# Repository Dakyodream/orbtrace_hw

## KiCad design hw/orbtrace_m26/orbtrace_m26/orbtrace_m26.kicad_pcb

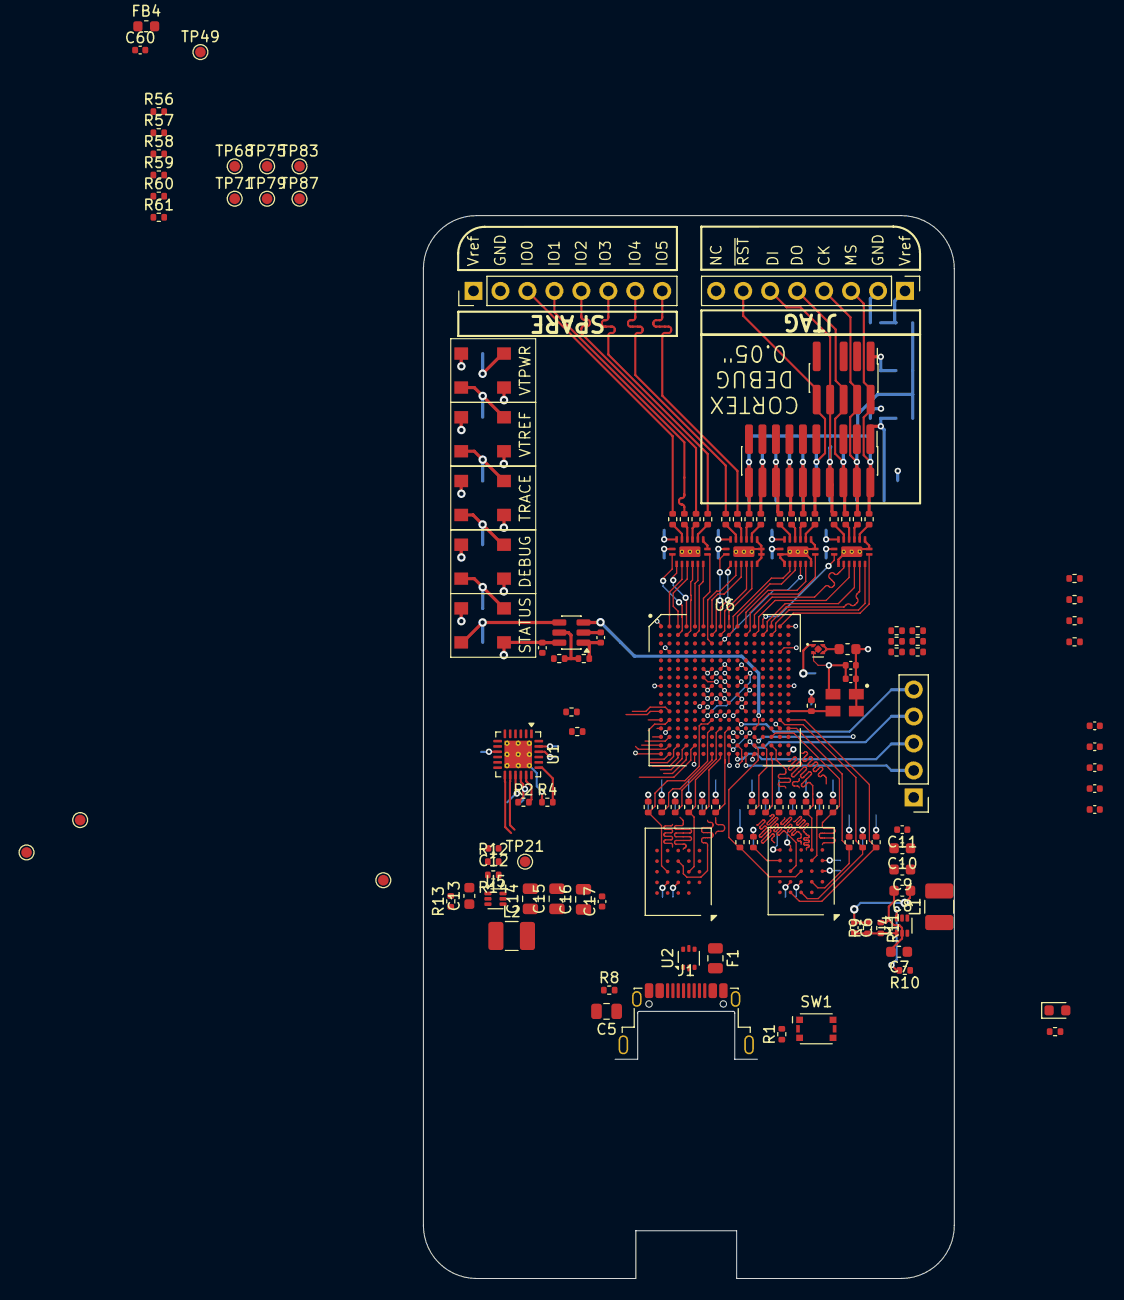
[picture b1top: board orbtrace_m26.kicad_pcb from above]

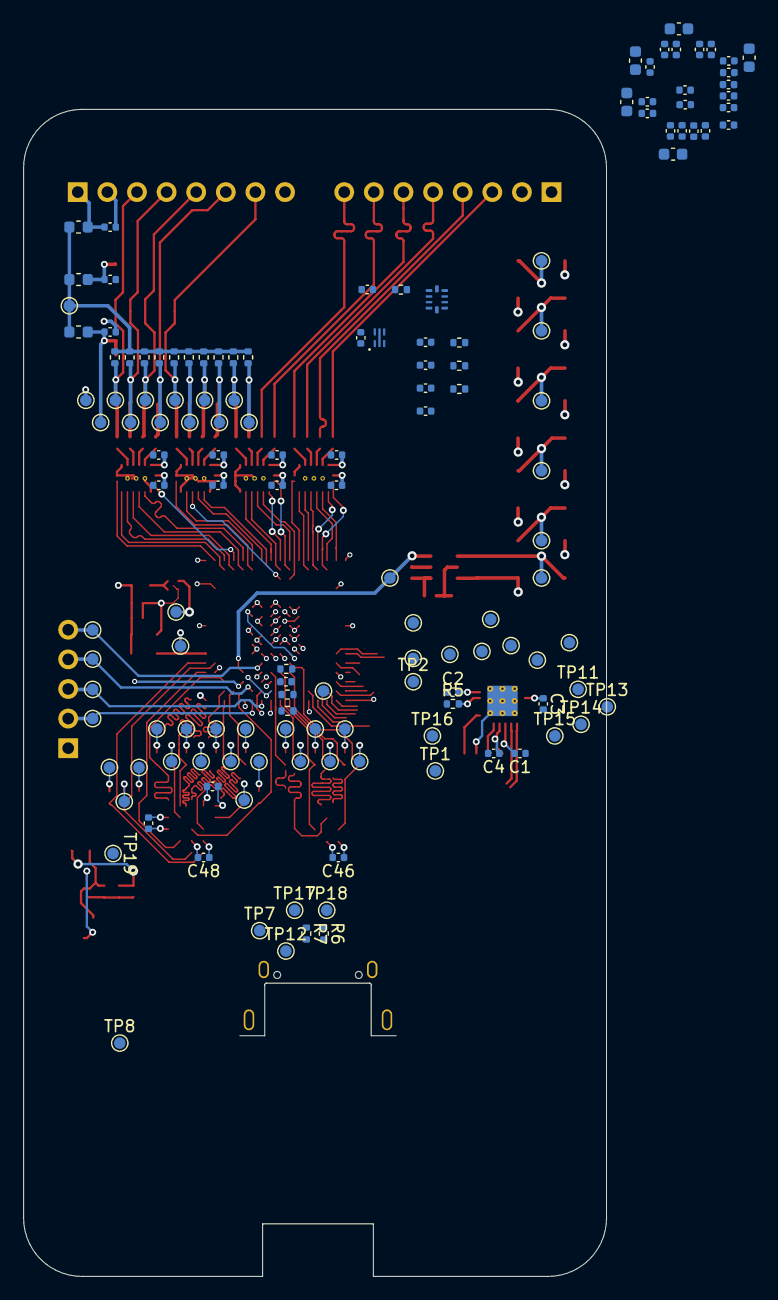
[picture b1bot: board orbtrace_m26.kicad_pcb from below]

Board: 4 copper layers, 50.0 x 100.1 mm, 273 parts (141 on the bottom side), 161 nets.

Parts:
C1, C2, C11, C17, C44: 1µF; C_0402_1005Metric
C3, C4, C18, C22, C23, C24, C25, C26, C27, C29, C30, C32, C33, C34, C35, C36, C37, C38, C39, C40, C41, C42, C43, C45, C46, C47, C48, C49, C50, C51, C52, C53, C54, C55, C56, C57, C58, C59, C60, C61, C62, C71, C72, C73, C74, C75, C76, C77: 100nF; C_0402_1005Metric
C5: 4.7nF; C_0805_2012Metric
C6, C12: 6.8pF; C_0402_1005Metric
C7, C13: 4.7µF; C_0603_1608Metric
C8, C9, C10, C19, C20, C21, C28, C31: 10µF; C_0603_1608Metric
C14, C15, C16: 22µF; C_0805_2012Metric
C63, C64, C65, C66: 470nF; C_0402_1005Metric
D1: GREEN; LED_0603_1608Metric
F1: 500mA; Fuse_0805_2012Metric
FB1, FB2, FB3, FB4, FB5: MMZ1005Y121CT000; L_0603_1608Metric
J1: USB_C_Receptacle_USB2.0_16P; USB_C_Receptacle_Amphenol_12401948E412A
J2: Conn_01x05; PinHeader_1x05_P2.54mm_Vertical
J3, J4: Conn_01x08; PinHeader_1x08_P2.54mm_Vertical
L1, L2: 2.2µH; L_1210_3225Metric_Pad1.42x2.65mm_HandSolder
R1, R5: 10k; R_0402_1005Metric
R2: 20k; R_0402_1005Metric
R3: 180Ω; R_0402_1005Metric
R4: 8.06k; R_0402_1005Metric
R6, R7: 5.1k; R_0402_1005Metric
R8: 1M; R_0402_1005Metric
R9: 453k; R_0402_1005Metric
R10, R13: 475k; R_0402_1005Metric
R11, R14, R38, R39, R40, R41, R44, R49, R52, R53, R54, R55, R56, R57, R58, R59, R60, R61: 100k; R_0402_1005Metric
R12: 82.5k; R_0402_1005Metric
R15, R16, R17, R18, R19, R20, R21, R22, R23, R24, R25, R26: 4.7k; R_0402_1005Metric
R27, R28, R29, R68, R69, R70, R71, R72, R73, R74, R75, R76, R77, R78, R79, R80, R81, R82, R83, R84, R85, R86: 0Ω; R_0402_1005Metric
R30, R31, R32, R33, R34, R35, R36, R37, R42, R43, R45, R46, R47, R48, R50, R51: 100Ω; R_0402_1005Metric
R62, R63, R64, R65, R66, R67: 1K; R_0402_1005Metric
SW1: SW_Push_Shielded; SW_Wurth_WS-TASV_435151014824
TP1, TP2, TP3, TP4, TP5, TP6, TP7, TP8, TP9, TP10, TP11, TP12, TP13, TP14, TP15, TP16, TP17, TP18, TP19, TP20, TP21, TP22, TP23, TP24, TP25, TP26, TP27, TP28, TP29, TP30, TP31, TP32, TP33, TP34, TP35, TP36, TP37, TP38, TP39, TP40, TP41, TP42, TP43, TP44, TP45, TP46, TP47, TP48, TP49, TP52, TP53, TP56, TP59, TP62, TP65, TP68, TP69, TP71, TP72, TP75, TP76, TP79, TP80, TP83, TP84, TP87, TP93, TP94, TP95, TP96, TP97, TP98, TP99, TP100, TP101, TP102, TP103: TestPoint_Pad_D1.0mm
U1: USB3343; QFN-24-1EP_4x4mm_P0.5mm_EP2.6x2.6mm_ThermalVias
U2: USBLC6-2P6; SOT-666
U3: TLV71325PDQN; Texas_X2SON-4_1x1mm_P0.65mm
U4, U5: TLV62568PDRL; SOT-563
U6: LFE5U-25F-6BG256C; lattice_caBGA-256_ECP5
U7: M24128-BFMH; UFDFPN5
U8: W956A8MBYA5I; BGA-24_6x8mm_Layout5x5_P1.0mm
U9: S25FL064LABBHV020; BGA-24_6x8mm_Layout5x5_P1.0mm
U10: SWD-TRACE-FTSH110; PinSocket_2x10_P1.27mm_JTAG
U11, U12, U14, U15: SN74AVC4T774-Q1; TI-WQFN-BQB0016B
U13: SWD-FTSH105; PinSocket_2x05_P1.27mm_JTAG
U16: TLA2024; RUG0010A
U17: SN74LVC1T45DBV; SOT-23-6
U18, U19, U20, U21, U22: WL-ICLED; LED_RGB_Wuerth-PLCC4_5x5mm_WL-ICLED
Y1: 831025497; CFPS-39

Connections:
+1V1: C12.1, C14.1, C15.1, C16.1, C17.1, C19.1, C20.1, C21.1, C22.1, C23.1, C24.1, C25.1, C26.1, C27.1, L2.2, R12.2, R62.2, TP21.1 (1_1), U6.G6 (VCC), U6.G7 (VCC), U6.G9 (VCC), U6.L8 (VCC), U6.L9 (VCC), U6.L10 (VCC)
+2V5: C28.1, C29.1, C30.1, R63.2, TP20.1 (1_1), U3.1 (OUT), U6.G11 (VCCAUX), U6.L7 (VCCAUX)
+3.3V: C3.1, C6.1, C8.1, C9.1, C10.1, C11.1, C31.1, C32.1, C33.1, C34.1, C35.1, C36.1, C37.1, C38.1, C39.1, C40.1, C41.1, C42.1, C43.1, C46.1, C47.1, C48.1, C49.1, C50.1, C52.1, C55.1, C57.1, C71.1, FB1.1, L1.2, R1.2, R9.2, R15.2, R16.2, R17.2, R18.2, R19.2, R21.2, R22.2, R23.2, R24.2, R25.2, R26.2, R64.2, R66.2, TP19.1 (1_1), U1.2 (CLKOUT), U1.9 (VDDIO), U3.3 (EN), U3.4 (IN), U6.F6 (VCCIO0), U6.F7 (VCCIO0), U6.F10 (VCCIO1), U6.F11 (VCCIO1), U6.H6 (VCCIO7), U6.H7 (VCCIO7), U6.J6 (VCCIO6), U6.J7 (VCCIO6), U6.K11 (VCCIO3), U6.L6 (VCCIO8), U6.L11 (VCCIO3), U7.1 (VCC), U8.B4 (VCC), U8.D1 (VCCQ), U8.E4 (VCCQ), U9.B4 (VCC), U11.16 (VCCA), U12.16 (VCCA), U14.16 (VCCA), U15.16 (VCCA), U17.1 (VCCA)
+5V: C4.1, C7.1, C13.1, C61.1, C72.1, C73.1, C74.1, C75.1, C76.1, C77.1, F1.1, R2.1, R3.2, R10.1, R13.1, TP7.1 (1_1), U1.16 (VBAT), U2.5 (VBUS), U4.3 (VIN), U4.5 (EN), U5.3 (VIN), U5.5 (EN), U16.8 (VDD), U17.6 (VCCB), U18.3 (VDD), U19.3 (VDD), U20.3 (VDD), U21.3 (VDD), U22.3 (VDD)
/FPGA/DONE: R22.1, TP22.1 (1_1), U6.P9 (DONE)
/USB/VBUS: F1.2, J1.A4 (VBUS), J1.A9 (VBUS), J1.B4 (VBUS), J1.B9 (VBUS), TP12.1 (1_1)
BTN: R1.1, SW1.2, TP8.1 (1_1), U6.P12 (PR47D)
CFG0: R24.1, R26.1, R27.2, R29.2, U6.N10 (CFG_0), U6.R10 (CFG_2)
CFG1: R25.1, R28.2, U6.P10 (CFG_1)
DEBUG_JTCK: U6.B13 (PT60A), U11.5 (A3)
DEBUG_JTDI: U6.A12 (PT53B), U11.3 (A1)
DEBUG_JTDO: U6.B12 (PT56A), U11.4 (A2)
DEBUG_JTMS: U6.A14 (PT65B), U11.6 (A4)
DEBUG_NRST: U6.A11 (PT35A), U14.6 (A4)
DIR_JTCK: U6.B14 (PT67A), U11.7 (DIR3)
DIR_JTDI: U6.A13 (PT65A), U11.1 (DIR1)
DIR_JTMS: U6.A15 (PT67B), U11.8 (DIR4)
DIR_NRST: U6.B11 (PT49A), U14.8 (DIR4)
GND: C1.1, C2.1, C3.2, C4.2, C5.2, C7.2, C8.2, C9.2, C10.2, C11.2, C13.2, C14.2, C15.2, C16.2, C17.2, C18.2, C19.2, C20.2, C21.2, C22.2, C23.2, C24.2, C25.2, C26.2, C27.2, C28.2, C29.2, C30.2, C31.2, C32.2, C33.2, C34.2, C35.2, C36.2, C37.2, C38.2, C39.2, C40.2, C41.2, C42.2, C43.2, C44.2, C45.2, C46.2, C47.2, C48.2, C49.2, C50.2, C51.2, C52.2, C53.2, C54.2, C55.2, C56.2, C57.2, C58.2, C59.2, C60.2, C61.2, C62.2, C63.2, C64.2, C65.2, C66.2, C71.2, C72.2, C73.2, C74.2, C75.2, C76.2, C77.2, D1.1 (K), J1.A1 (GND), J1.A12 (GND), J1.B1 (GND), J1.B12 (GND), J2.1, J3.2, J4.2, R4.1, R5.1, R6.1, R7.1, R8.1, R11.1, R14.1, R20.1, R27.1, R28.1, R29.1, R67.1, SW1.1, SW1.SH (B), TP100.1 (1_1), TP101.1 (1_1), TP102.1 (1_1), U1.25 (GND), U2.2 (GND), U3.2 (GND), U3.5 (PAD), U4.2 (GND), U5.2 (GND), U6.A1 (GND), U6.A16 (GND), U6.D2 (GND), U6.D15 (GND), U6.F8 (GND), U6.F9 (GND), U6.G8 (GND), U6.G10 (GND), U6.H1 (GND), U6.H8 (GND), U6.H9 (GND), U6.H10 (GND), U6.H11 (VCCIO2), U6.H16 (GND), U6.J8 (GND), U6.J9 (GND), U6.J10 (GND), U6.J11 (VCCIO2), U6.K6 (GND), U6.K7 (GND), U6.K8 (GND), U6.K9 (GND), U6.K10 (GND), U6.N2 (GND), U6.N15 (GND), U6.T1 (GND), U6.T5 (GND), U6.T12 (GND), U6.T16 (GND), U7.2 (VSS), U7.5 (~WC), U8.B1 (~CLK), U8.B3 (VSS), U8.C1 (VSSQ), U8.E5 (VSSQ), U9.B3 (GND), U10.3 (GND), U10.5 (GND), U10.9 (GNDDET), U10.15 (GND), U10.17 (GND), U10.19 (GND), U11.2 (DIR2), U11.9 (~OE), U11.10 (GND), U11.17 (TP), U12.7 (DIR3), U12.8 (DIR4), U12.9 (~OE), U12.10 (GND), U12.17 (TP), U13.3 (GND), U13.5 (GND), U13.9 (GNDDET), U14.1 (DIR1), U14.2 (DIR2), U14.7 (DIR3), U14.9 (~OE), U14.10 (GND), U14.17 (TP), U15.9 (~OE), U15.10 (GND), U15.17 (TP), U16.1 (ADDR), U16.3 (GND), U17.2 (GND), U18.1 (GND), U19.1 (GND), U20.1 (GND), U21.1 (GND), U22.1 (GND), Y1.2 (GND)
HRAM_CLK: R77.1, U6.N16 (PR32A), U8.B2 (CLK)
HRAM_CS: R76.1, U6.M15 (PR26D), U8.A3 (~CS)
HRAM_DQ0: R78.1, U6.T15 (PR38D), U8.D3 (DQ0)
HRAM_DQ1: R79.1, U6.P13 (PR41A), U8.D2 (DQ1)
HRAM_DQ2: R80.1, U6.T14 (PR41D), U8.C4 (DQ2)
HRAM_DQ3: R81.1, U6.R13 (PR41C), U8.D4 (DQ3)
HRAM_DQ4: R82.1, U6.T13 (PR44B), U8.D5 (DQ4)
HRAM_DQ5: R83.1, U6.R14 (PR41B), U8.E3 (DQ5)
HRAM_DQ6: R84.1, U6.R15 (PR38C), U8.E2 (DQ6)
HRAM_DQ7: R85.1, U6.P14 (PR38B), U8.E1 (DQ7)
HRAM_RST: R74.1, U6.M16 (PR26C), U8.A4 (~RESET)
HRAM_RWDS: R75.1, U6.R12 (PR44A), U8.C3 (RWDS)
JTCK: J2.3, R20.2, TP36.1 (1_1), U6.T10 (TCK)
JTDI: J2.4, R18.1, TP40.1 (1_1), U6.R11 (TDI)
JTDO: J2.5, R19.1, TP44.1 (1_1), U6.M10 (TDO)
JTMS: J2.2, R17.1, TP32.1 (1_1), U6.T11 (TMS)
LED_DATA: TP93.1 (1_1), U6.N12 (PR44D), U17.3 (A)
LED_EXT: TP99.1 (1_1), U22.4 (DOUT)
LED_START: TP94.1 (1_1), U17.4 (B), U18.2 (DIN)
unnamed: D1.2 (A), R3.1
unnamed: J1.A5 (CC1), R6.2
unnamed: J1.B5 (CC2), R7.2
unnamed: C5.1, J1.SH (SHIELD), R8.2
unnamed: C60.1, FB4.2, J3.1, TP49.1 (1_1)
unnamed: C62.1, FB5.1, J4.1
unnamed: R68.2, TP28.1 (1_1)
unnamed: R69.2, TP30.1 (1_1)
unnamed: R70.2, TP33.1 (1_1)
unnamed: R71.2, TP37.1 (1_1)
unnamed: R72.2, TP41.1 (1_1)
unnamed: R73.2, TP45.1 (1_1)
unnamed: R74.2, TP34.1 (1_1)
unnamed: R75.2, TP38.1 (1_1)
unnamed: R76.2, TP42.1 (1_1)
unnamed: R77.2, TP46.1 (1_1)
unnamed: R78.2, TP26.1 (1_1)
unnamed: R79.2, TP27.1 (1_1)
unnamed: R80.2, TP29.1 (1_1)
unnamed: R81.2, TP31.1 (1_1)
unnamed: R82.2, TP35.1 (1_1)
unnamed: R83.2, TP39.1 (1_1)
unnamed: R84.2, TP43.1 (1_1)
unnamed: R85.2, TP47.1 (1_1)
unnamed: R86.2, TP23.1 (1_1)
unnamed: C1.2, U1.15 (VDD33), U1.18 (ID)
unnamed: R4.2, U1.19 (RBIAS)
unnamed: R2.2, U1.17 (VBUS)
unnamed: C2.2, U1.23 (VDD18)
unnamed: C6.2, R9.1, R11.2, U4.1 (FB)
unnamed: R10.2, U4.6 (PG)
unnamed: L1.1, U4.4 (SW)
unnamed: C12.2, R12.1, R14.2, U5.1 (FB)
unnamed: R13.2, U5.6 (PG)
unnamed: L2.1, U5.4 (SW)
unnamed: R23.1, U6.T9 (INITN)
unnamed: C54.1, FB2.1, TP103.1 (1_1), U10.1 (VTREF)
unnamed: R34.1, U11.14 (B1)
unnamed: R36.1, U11.13 (B2)
unnamed: R30.1, U11.12 (B3)
unnamed: R32.1, U11.11 (B4)
unnamed: R35.1, U12.14 (B1)
unnamed: R37.1, U12.13 (B2)
unnamed: R31.1, U12.12 (B3)
unnamed: R33.1, U12.11 (B4)
unnamed: C59.1, FB3.2, U13.1 (VTREF)
unnamed: R47.1, U14.14 (B1)
unnamed: R50.1, U14.13 (B2)
unnamed: R42.1, U14.12 (B3)
unnamed: R45.1, U14.11 (B4)
unnamed: R48.1, U15.14 (B1)
unnamed: R51.1, U15.13 (B2)
unnamed: R43.1, U15.12 (B3)
unnamed: R46.1, U15.11 (B4)
unnamed: C63.1, R62.1, U16.4 (AN0)
unnamed: C64.1, R63.1, U16.5 (AN1)
unnamed: C65.1, R64.1, U16.6 (AN2)
unnamed: C66.1, R65.1, U16.7 (AN3)
unnamed: R66.1, R67.2, U17.5 (DIR)
unnamed: TP95.1 (1_1), U18.4 (DOUT), U19.2 (DIN)
unnamed: TP96.1 (1_1), U19.4 (DOUT), U20.2 (DIN)
unnamed: TP97.1 (1_1), U20.4 (DOUT), U21.2 (DIN)
unnamed: TP98.1 (1_1), U21.4 (DOUT), U22.2 (DIN)
unnamed: C44.1, C45.1, FB1.2, Y1.1 (EN), Y1.4 (+Vs)
PROGRAMN: C18.1, R21.1, TP48.1 (1_1), U6.P11 (PR47C), U6.R9 (PROGRAMN)
QSPI_CS: R73.1, U6.N8 (PB15A), U9.C2 (~CS)
QSPI_IO0: R68.1, U6.T8 (PB11B), U9.D3 (IO0)
QSPI_IO1: R69.1, U6.T7 (PB11A), U9.D2 (IO1)
QSPI_IO2: R70.1, U6.M7 (PB9B), U9.C4 (IO2)
QSPI_IO3: R71.1, U6.N7 (PB9A), U9.D4 (IO3)
QSPI_SCK: R72.1, U6.N9 (CCLK), U9.B2 (CLK)
SCL: R15.1, TP25.1 (1_1), U6.L2 (PL26B), U7.4 (SCL), U16.10 (SCL)
SDA: R16.1, TP24.1 (1_1), U6.L1 (PL26A), U7.3 (SDA), U16.9 (SDA)
SPARE_DIR0: U6.B3 (PT4B), U15.1 (DIR1)
SPARE_DIR1: U6.A4 (PT6B), U15.2 (DIR2)
SPARE_DIR2: U6.B5 (PT15B), U15.7 (DIR3)
SPARE_DIR3: U6.A6 (PT18B), U15.8 (DIR4)
SPARE_DIR4: U6.B7 (PT27B), U12.1 (DIR1)
SPARE_DIR5: U6.A8 (PT29B), U12.2 (DIR2)
SPARE_IO0: U6.A2 (PT4A), U15.3 (A1)
SPARE_IO1: U6.A3 (PT6A), U15.4 (A2)
SPARE_IO2: U6.B4 (PT11B), U15.5 (A3)
SPARE_IO3: U6.A5 (PT18A), U15.6 (A4)
SPARE_IO4: U6.C7 (PT27A), U12.3 (A1)
SPARE_IO5: U6.A7 (PT29A), U12.4 (A2)
SYS_CLK: R86.1, U6.L16 (PR26A), Y1.3 (out)
TRACE_CLK: U6.C8 (PT35A), U14.5 (A3)
TRACE_D0: U6.A10 (PT42B), U14.4 (A2)
TRACE_D1: U6.B9 (PT38A), U14.3 (A1)
TRACE_D2: U6.A9 (PT42A), U12.6 (A4)
TRACE_D3: U6.B8 (PT35B), U12.5 (A3)
ULPI_CLK: TP1.1 (1_1), U1.21 (REFCLK/XI), U6.R5 (PL44A)
ULPI_DATA0: TP5.1 (1_1), U1.4 (DATA0), U6.T2 (PL38D)
ULPI_DATA1: TP6.1 (1_1), U1.5 (DATA1), U6.R2 (PL38C)
ULPI_DATA2: TP9.1 (1_1), U1.6 (DATA2), U6.R1 (PL35B)
ULPI_DATA3: TP10.1 (1_1), U1.7 (DATA3), U6.P2 (PL32B)
ULPI_DATA4: TP11.1 (1_1), U1.8 (DATA4), U6.P1 (PL35A)
ULPI_DATA5: TP13.1 (1_1), U1.10 (DATA5), U6.N1 (PL32A)
ULPI_DATA6: TP14.1 (1_1), U1.11 (DATA6), U6.M2 (PL26D)
ULPI_DATA7: TP15.1 (1_1), U1.12 (DATA7), U6.M1 (PL26C)
ULPI_DIR: TP4.1 (1_1), U1.1 (DIR), U6.T3 (PL41D)
ULPI_NXT: TP3.1 (1_1), U1.3 (NXT), U6.R3 (PL41B)
ULPI_RESET: R5.2, TP16.1 (1_1), U1.22 (~RESETB), U6.T4 (PL44B)
ULPI_STP: TP2.1 (1_1), U1.24 (STP), U6.R4 (PL41C)
USB_D_N: J1.A7 (D-), J1.B7 (D-), TP18.1 (1_1), U1.14 (DM), U2.1 (IO1), U2.6 (IO1)
USB_D_P: J1.A6 (D+), J1.B6 (D+), TP17.1 (1_1), U1.13 (DP), U2.3 (IO2), U2.4 (IO2)
VTREF: C51.1, C53.1, C56.1, C58.1, FB2.2, FB3.1, FB4.1, FB5.2, R38.2, R39.2, R40.2, R41.2, R44.2, R49.2, R52.2, R53.2, R54.2, R55.2, R56.2, R57.2, R58.2, R59.2, R60.2, R61.2, R65.2, TP52.1 (1_1), U11.15 (VCCB), U12.15 (VCCB), U14.15 (VCCB), U15.15 (VCCB)
VT_DEBUG_JTCK: J4.4, R30.2, R40.1, TP59.1 (1_1), U10.4 (SWCLK), U13.4 (SWCLK)
VT_DEBUG_JTDI: J4.6, R34.2, R44.1, TP65.1 (1_1), U10.8 (NC_(JTDI)), U13.8 (NC_(JTDI))
VT_DEBUG_JTDO: J4.5, R36.2, R41.1, TP62.1 (1_1), U10.6 (SWO), U13.6 (SWO)
VT_DEBUG_JTMS: J4.3, R32.2, R39.1, TP56.1 (1_1), U10.2 (SWDIO), U13.2 (SWDIO)
VT_DEBUG_NRST: J4.7, R38.1, R45.2, TP53.1 (1_1), U10.10 (NRST), U13.10 (NRST)
VT_SPARE_IO0: J3.3, R48.2, R56.1, TP68.1 (1_1)
VT_SPARE_IO1: J3.4, R51.2, R57.1, TP71.1 (1_1)
VT_SPARE_IO2: J3.5, R43.2, R58.1, TP75.1 (1_1)
VT_SPARE_IO3: J3.6, R46.2, R59.1, TP79.1 (1_1)
VT_SPARE_IO4: J3.7, R35.2, R60.1, TP83.1 (1_1)
VT_SPARE_IO5: J3.8, R37.2, R61.1, TP87.1 (1_1)
VT_TRACE_CLK: R42.2, R49.1, TP69.1 (1_1), U10.12 (VT_TRACECLK)
VT_TRACE_D0: R50.2, R52.1, TP72.1 (1_1), U10.14 (TRACED0)
VT_TRACE_D1: R47.2, R53.1, TP76.1 (1_1), U10.16 (TRACED1)
VT_TRACE_D2: R33.2, R54.1, TP80.1 (1_1), U10.18 (TRACED2)
VT_TRACE_D3: R31.2, R55.1, TP84.1 (1_1), U10.20 (TRACED3)
